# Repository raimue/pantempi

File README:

===== pantempi =====

pantempi is a temperature and humidity sensor board based on the panStamp
wireless sensor nodes.

==== git submodule configuration ====

This repository uses external repostiories using git submodules:

 $ git submodule init
 $ git submodule update

==== Hardware Assembly ====

Each panStamp needs an antenna. A simple wire stub should do. The default
frequency is 868 MHz, but they can also operate on 915 MHz if you chose so
later on.

                 |  868 MHz | 915 MHz  |
  ---------------+----------+----------+
  1/4 Wavelength |  82.2 mm |  77.9 mm |
  1/2 Wavelength | 164.3 mm | 155.9 mm |

In experiments it seems like that these do not have to be very exact on short
distance, so any wirelength around 8 cm should do.

(Source: http://code.google.com/p/panstamp/wiki/antennalengths)

==== Software Requirements ====

* Arduino IDE

While the Arduino-Makefile used in this project allows to compile the firmware
from the command line without use of the Arduino IDE, the toolchain and Arduino
core libraries are still required. The Makefile detects an existing
installation Arduino IDE installation and uses its resources. Your mileage may
vary.

  http://arduino.cc/en/Main/Software

* Arduino panstamp library

This is required for the pantempi firmware. Import library with the help of the
Arduino IDE or simply place the panstamp folder in this ZIP file into the
.../arduino/libraries/ directory (detailed installation instructions can be
found at http://arduino.cc/en/Guide/Libraries).

DO NOT USE THE LIBRARY FROM THE SUBVERSION OR tools/panstamp/arduino/.
Apparently EEPROM handling is broken in this version at the moment and
therefore new nodes with this firmware cannot be configured remotely. Use the
release from the panStamp website.

  http://www.panstamp.com/downloads/panstamp_library.zip?attredirects=0&d=1

* Arduino Timer1 library

This is required for the modem firmware. See instructins above.

  http://playground.arduino.cc/code/timer1

* panStamp Python applications

The host software components are already available in tools/panstamp/python
after initializing the git submodules as described above. While the upstream
release should work, the local branch contains portability fixes for
pyswapdmtgui. Additionally it fixes pyswapdmt which offers a command line
interface to sniff and monitor SWAP traffic and configure nodes.

The python applications have their own requirements, depending on which tool
you want to use you will need python >= 2.6, wxPython >=2.8, and pyserial.

  (http://www.panstamp.com/downloads/panStamp_apps.zip?attredirects=0&d=1)

==== Building & Flashing ====

...

==== Deployment ====

...

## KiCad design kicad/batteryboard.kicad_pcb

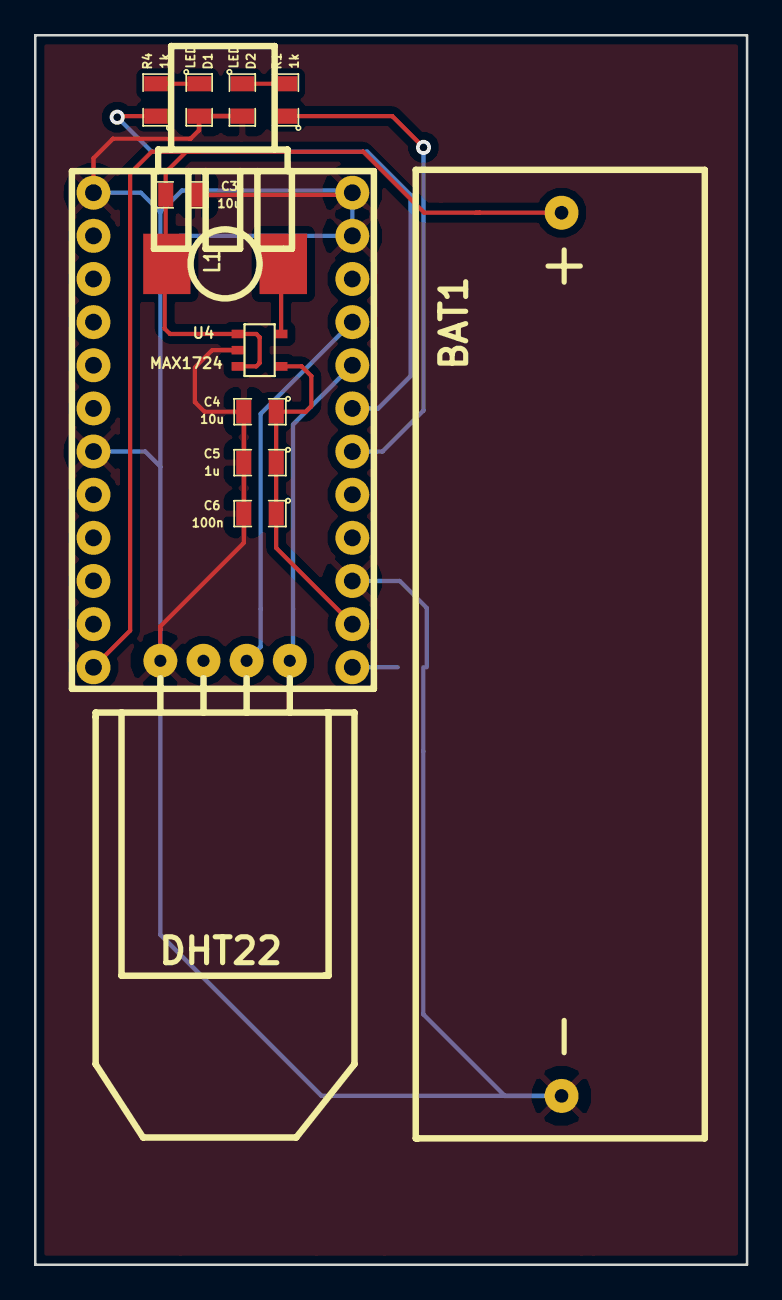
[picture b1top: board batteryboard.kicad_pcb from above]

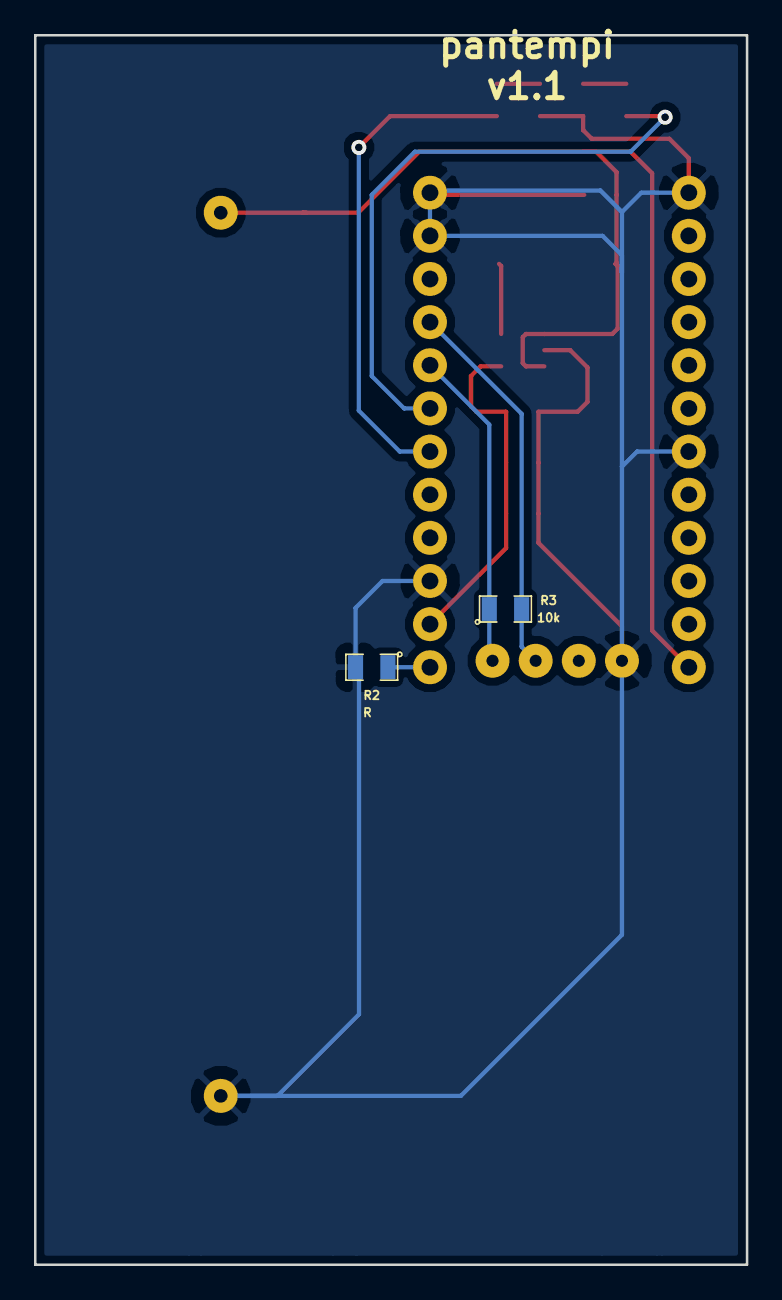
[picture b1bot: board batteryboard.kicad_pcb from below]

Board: 2 copper layers, 41.9 x 72.4 mm, 15 parts (2 on the bottom side), 11 nets.

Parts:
BAT1: CONN_2; 12BH311P
C3, C4: 10u; SM0805
C5: 1u; SM0805
C6: 100n; SM0805
D1, D2: LED; SM0805
L1: 10u; Pulse_P0770NL
R1, R4: 1k; SM0805
R2: R; SM0805
R3: 10k; SM0805
U1: PANSTAMP_02
U3: DHT22
U4: MAX1724; SOT23-5

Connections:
+3.3V: C4.1, C5.1, C6.1, U1.14, U4.4
/A1: R3.2, U1.21, U3.2
/A2: R3.1, U1.20, U3.1
/BATTERY: BAT1.1, C3.1, L1.1, U1.12, U4.1, U4.3
/LED1: R1.1, U1.18
/LED2: R4.1, U1.19
/RESET: R2.1, U1.13
GND: BAT1.2, C3.2, C4.2, C5.2, C6.2, D1.2, D2.2, R2.2, U1.1, U1.7, U1.15, U1.23, U1.24, U3.4, U4.2
unnamed: D2.1, R1.2
unnamed: D1.1, R4.2
unnamed: L1.2, U4.5

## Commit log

2014-01-25 Add initial README file
2014-01-25 Initial import
2014-01-25 Import modem from panstamp sketches
2014-01-25 Restructure directories
2014-01-26 Add Arduino-Makefile as a submodule
2014-01-26 Remove trailing whitespace
2014-01-26 README: Add quick note about submodules
2014-01-26 Ignore build directories
2014-01-26 modem: Add forward declarations
    This brings the source closer to standard C++ code that can be compiled
    with the Arduino-Makefile from command line.
2014-01-26 pantempi: Convert .ino to .cpp for Arduino-Makefile
    The Arduino-Makefile can only handle a single .ino file for each
    project. Therefore, convert the libraries to a .cpp file extension and
    make adjustments to allow compilation with either the Arduino IDE or the
    Arduino-Makefile from command line.
2014-01-26 Configuration for Arduino-Makefile
2014-01-26 README: Change table layout slightly
2014-01-26 Import panStamp Subversion repository mirror
    Track the pantempi branch of the panStamp Subversion mirror which
    already contains fixes to the tools provided upstream.
2014-01-26 pyswapdmt.sh: Launcher script for pyswapdmt.py
2014-01-26 pyswapdmtgui.sh: Launcher script for pyswapdmtgui
2014-01-26 Update submodule for panstamp tools
2014-01-26 README: Update list of dependencies
2014-01-26 README: Initial conversion to MarkDown syntax
2014-01-27 add kicad files for batteryboard
2014-01-27 Update panstamp submodule
2014-01-28 change ports for sensor and battery sensing
2014-01-28 reroute path for battery sensing
2014-01-28 add text
2014-01-28 change pad sizes for easy soldering
2014-02-01 README: Fix typos and table layout
2014-02-04 rearrange some modules
2014-02-04 update version number
2014-02-04 add panel
2014-02-16 Ignore README.html
    This file may temporarily be created when converting the README.md
    markdown syntax in order to check whether it is valid.
2014-10-12 tools/panstamp: Switch to official git master
2014-10-12 tools/arduino-mk: Update to 1.3.4
2014-10-12 Disable LEDs to save energy
2014-12-23 Use rlwrap for swapdmt-cmd tool
2015-01-03 Update kicad files for pantempi v1.1
    Committing these as obtained from Peter.
2015-01-03 Move VOLT_SUPPLY_A7 to sensor.h
